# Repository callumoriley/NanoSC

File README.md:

# NanoSC
A brushless DC motor driver/speed controller based around the Arduino Nano

Note: there are 3 firmware versions using different timing schemes. There is BLDC_driver, which just uses delays and millis() for the timing events, and there are BLDC_driver_timer and BLDC_driver_timer_2 that use the ATMega328P's hardware timers and interrupts for the time events. BLDC_driver_timer uses only timer interrupts for its timing events and BLDC_driver_timer_2 uses timer interrupts for the commutation loop but micros() for the PWM signal generation.

Paradoxically, BLDC_driver seems to be the best at driving motors right now, as using the software timed events has a wider range of commutation frequencies that it can work at, but the timer versions were good opportunities to learn about AVR hardware timers.

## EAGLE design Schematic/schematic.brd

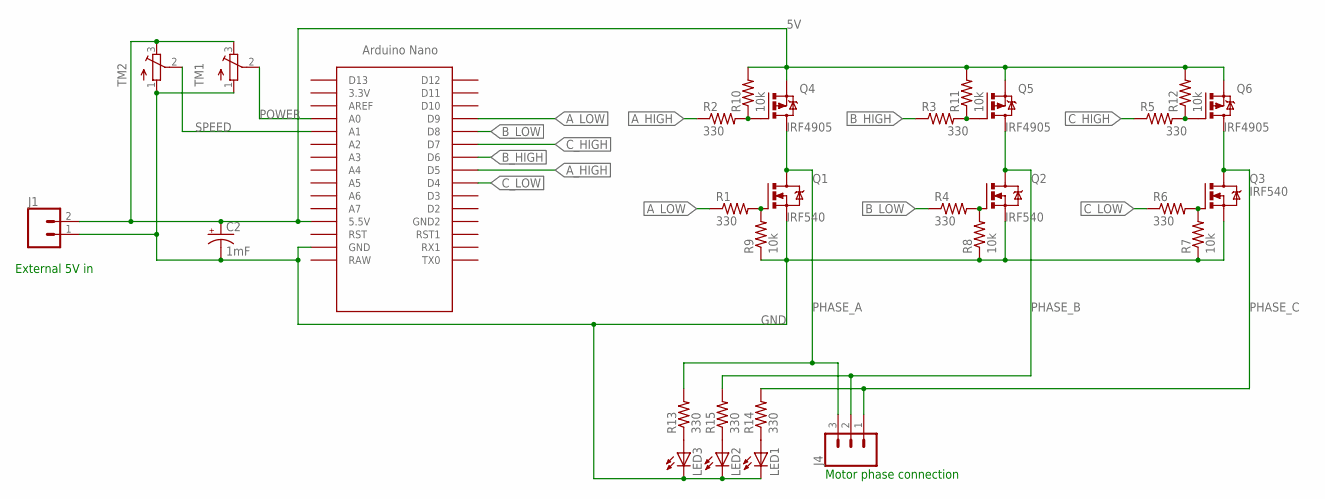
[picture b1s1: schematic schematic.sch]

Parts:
C2: 1mF; CPOL-RADIAL-5MM-10MM
J1: CONN_025MM; SCREWTERMINAL-5MM-2
J4: CONN_03-SCREW-5MM; SCREWTERMINAL-5MM-3
LED1, LED2, LED3: LED5MM
Q1, Q2, Q3: IRF540; TO220BV
Q4, Q5, Q6: IRF4905; TO220BH
R1, R2, R3, R4, R5, R6, R13, R14, R15: 330; 0204/5
R7, R8, R9, R10, R11, R12: 10k; 0204/5
TM1, TM2: TRIMPOT3386; TRIM-3386
U$1: NANO

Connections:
5V: C2.+, J1.2, Q4.S, Q5.S, Q6.S, R10.2, R11.2, R12.2, TM1.3 (E), TM2.3 (E), U$1.5V (5.5V)
A_HIGH: R2.1, U$1.D5
A_LOW: R1.1, U$1.D9
B_HIGH: R3.1, U$1.D6
B_LOW: R4.1, U$1.D8
C_HIGH: R5.1, U$1.D7
C_LOW: R6.1, U$1.D4
GND: C2.-, J1.1, LED1.K (C), LED2.K (C), LED3.K (C), Q1.S, Q2.S, Q3.S, R7.1, R8.1, R9.1, TM1.1 (A), TM2.1 (A), U$1.GND
unnamed: Q1.G, R1.2, R9.2
unnamed: Q4.G, R2.2, R10.1
unnamed: Q5.G, R3.2, R11.1
unnamed: Q2.G, R4.2, R8.2
unnamed: Q6.G, R5.2, R12.1
unnamed: Q3.G, R6.2, R7.2
unnamed: LED1.A, R14.1
unnamed: LED2.A, R15.1
unnamed: LED3.A, R13.1
PHASE_A: J4.3, Q1.D, Q4.D, R13.2
PHASE_B: J4.2, Q2.D, Q5.D, R15.2
PHASE_C: J4.1, Q3.D, Q6.D, R14.2
POWER: TM1.2 (S), U$1.A0
SPEED: TM2.2 (S), U$1.A1

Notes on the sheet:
External 5V in
Motor phase connection

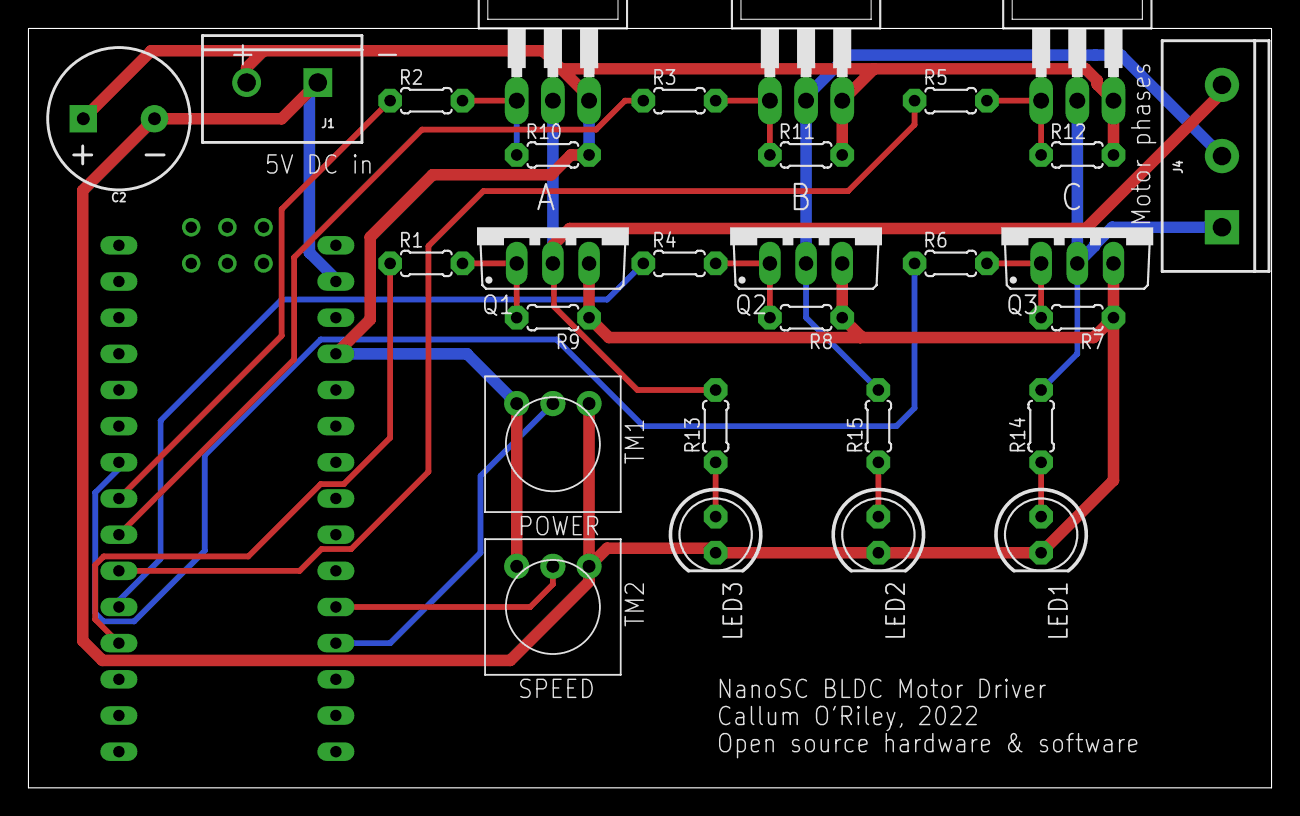
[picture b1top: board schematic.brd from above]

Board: 2 copper layers, 87.3 x 53.3 mm, 30 parts (0 on the bottom side), 22 nets.

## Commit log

2022-03-20 Create LICENSE

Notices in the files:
parts and their libraries:
SparkFun-Connectors: Licensing: Creative Commons ShareAlike 4.0 International - https://creativecommons.org/licenses/by-sa/4.0
